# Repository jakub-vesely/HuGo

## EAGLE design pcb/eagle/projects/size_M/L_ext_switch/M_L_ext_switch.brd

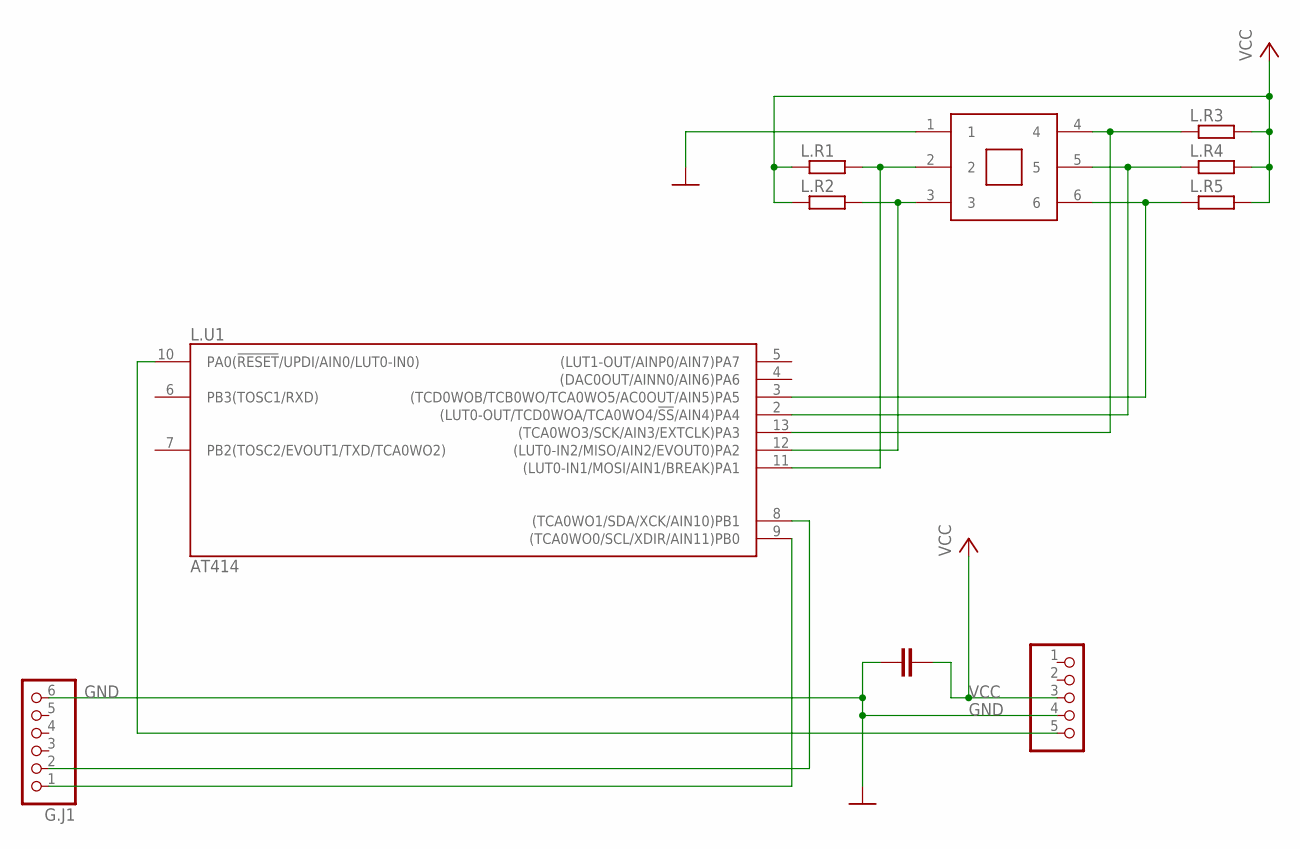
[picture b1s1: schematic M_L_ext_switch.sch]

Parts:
G.J1: PINHD-1X6; 1X06
G.J2: PINHD-1X5; 1X05
L.C1: 100n; C0603
L.R1, L.R2, L.R3, L.R4, L.R5: R-EU_R0603; R0603
L.SW1: 5_WAY_SWITCH
L.U1: AT414; SO14

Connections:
GND: G.J1.6, G.J2.4, L.C1.1, L.SW1.1, L.U1.14 (GND)
unnamed: G.J1.1, L.U1.9 ((TCA0WO0/SCL/XDIR/AIN11)PB0)
unnamed: G.J1.2, L.U1.8 ((TCA0WO1/SDA/XCK/AIN10)PB1)
unnamed: G.J2.5, L.U1.10 (PA0(!RESET!/UPDI/AIN0/LUT0-IN0))
unnamed: L.R5.1, L.SW1.6, L.U1.3 ((TCD0WOB/TCB0WO/TCA0WO5/AC0OUT/AIN5)PA5)
unnamed: L.R4.1, L.SW1.5, L.U1.2 ((LUT0-OUT/TCD0WOA/TCA0WO4/!SS!/AIN4)PA4)
unnamed: L.R3.1, L.SW1.4, L.U1.13 ((TCA0WO3/SCK/AIN3/EXTCLK)PA3)
unnamed: L.R2.2, L.SW1.3, L.U1.12 ((LUT0-IN2/MISO/AIN2/EVOUT0)PA2)
unnamed: L.R1.2, L.SW1.2, L.U1.11 ((LUT0-IN1/MOSI/AIN1/BREAK)PA1)
VCC: G.J2.3, L.C1.2, L.R1.1, L.R2.1, L.R3.2, L.R4.2, L.R5.2, L.U1.1 (VCC)

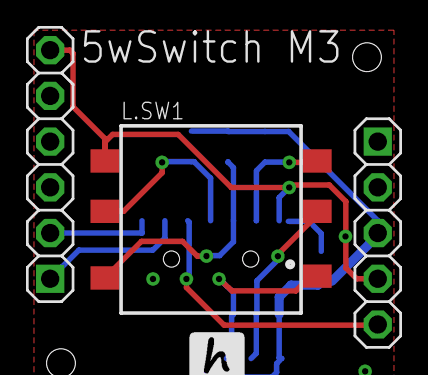
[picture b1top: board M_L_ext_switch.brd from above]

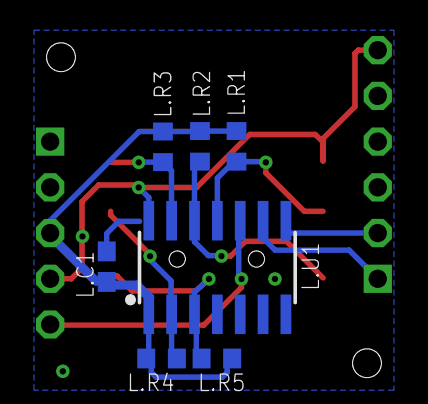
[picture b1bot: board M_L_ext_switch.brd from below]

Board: 2 copper layers, 10 parts (7 on the bottom side), 10 nets.

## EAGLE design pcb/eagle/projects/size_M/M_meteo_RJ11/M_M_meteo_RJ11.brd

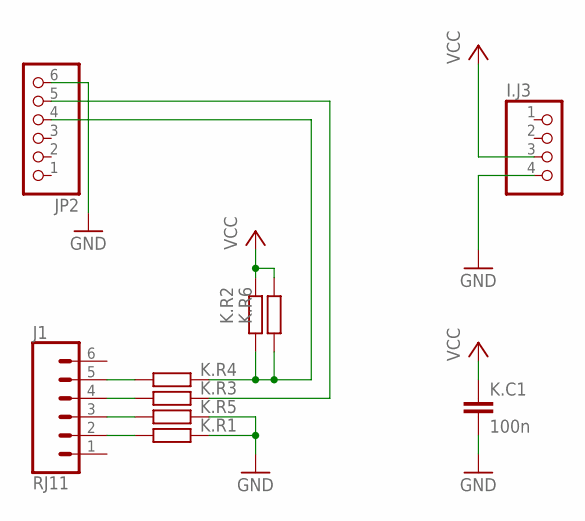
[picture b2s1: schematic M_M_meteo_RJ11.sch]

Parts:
I.J3: PINHD-1X4; 1X04
J1: RJ11; RJ11-6
JP2: PINHD-1X6; 1X06
K.C1: 100n; C0603
K.R1, K.R3, K.R4, K.R5: 1k; R0603
K.R2, K.R6: 4k7; R0603

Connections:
GND: I.J3.4, JP2.6, K.C1.2, K.R1.1, K.R5.1
unnamed: J1.5, K.R4.2
unnamed: JP2.5, K.R3.1
unnamed: JP2.4, K.R2.2, K.R4.1, K.R6.2
unnamed: J1.4, K.R3.2
unnamed: J1.3, K.R5.2
unnamed: J1.2, K.R1.2
VCC: I.J3.3, K.C1.1, K.R2.1, K.R6.1

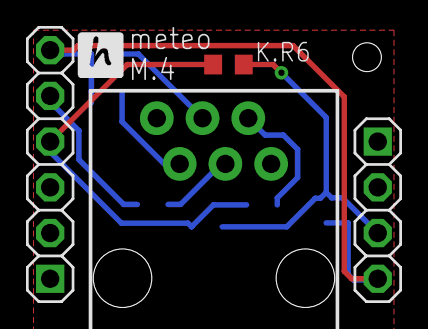
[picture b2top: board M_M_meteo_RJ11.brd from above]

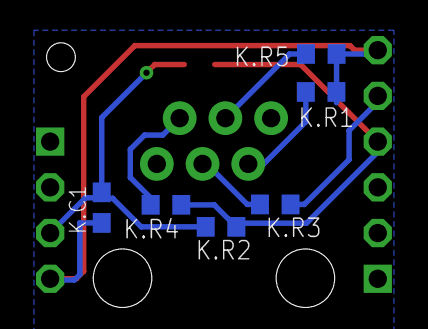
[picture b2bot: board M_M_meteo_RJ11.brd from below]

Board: 2 copper layers, 10 parts (6 on the bottom side), 8 nets.

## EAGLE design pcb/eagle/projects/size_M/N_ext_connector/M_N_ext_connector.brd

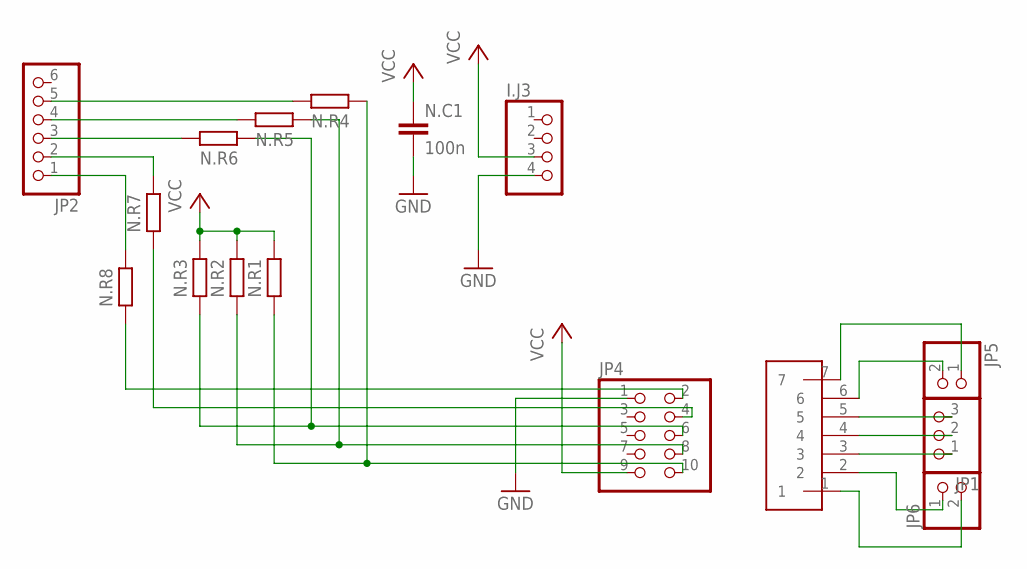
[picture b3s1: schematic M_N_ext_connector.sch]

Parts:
I.J3: PINHD-1X4; 1X04
JP1: PINHD-1X3; 1X03
JP2: PINHD-1X6; 1X06
JP4: PINHD-2X5/90; 2X05/90
JP5, JP6: PINHD-1X2; 1X02
N.C1: 100n; C0603
N.R1, N.R2, N.R3, N.R4, N.R5, N.R6, N.R7, N.R8: 4k7; R0603
U$1: 7PIN_CONNECTOR

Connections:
GND: I.J3.4, JP4.1, N.C1.2
GND1: JP5.1, U$1.7
unnamed: JP4.10, N.R1.2, N.R4.2
unnamed: JP4.8, N.R2.2, N.R5.2
unnamed: JP2.5, N.R4.1
unnamed: JP2.4, N.R5.1
unnamed: JP2.3, N.R6.1
unnamed: JP2.2, N.R7.1
unnamed: JP2.1, N.R8.1
unnamed: JP4.6, N.R3.2, N.R6.2
unnamed: JP4.4, N.R7.2
unnamed: JP4.2, N.R8.2
PA3: JP6.1, U$1.2
PA6: JP1.1, U$1.3
PA7: JP1.2, U$1.4
SCL1: JP5.2, U$1.6
SDA1: JP1.3, U$1.5
VCC: I.J3.3, JP4.9, N.C1.1, N.R1.1, N.R2.1, N.R3.1
VCC1: JP6.2, U$1.1

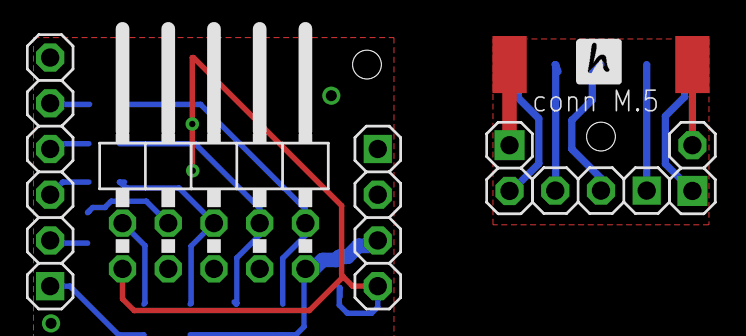
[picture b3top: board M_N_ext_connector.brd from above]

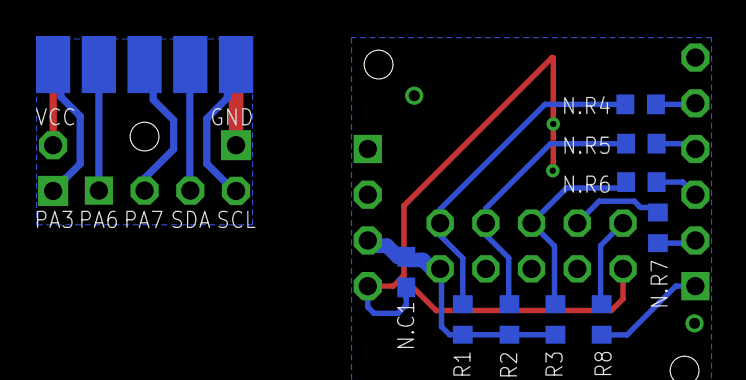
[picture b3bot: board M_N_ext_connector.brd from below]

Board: 2 copper layers, 16 parts (9 on the bottom side), 19 nets.

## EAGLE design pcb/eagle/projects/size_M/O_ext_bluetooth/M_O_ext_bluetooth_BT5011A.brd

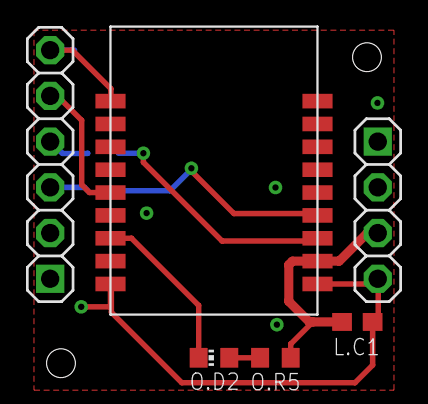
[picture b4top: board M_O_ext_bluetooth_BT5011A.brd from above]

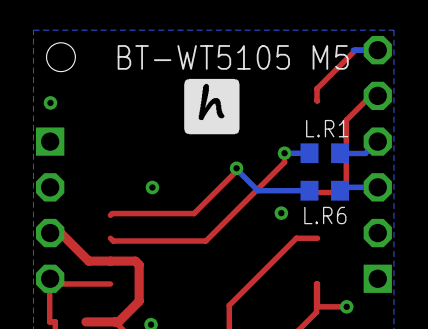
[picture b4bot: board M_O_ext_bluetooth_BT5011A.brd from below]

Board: 2 copper layers, 8 parts (2 on the bottom side), 9 nets.

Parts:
G.J1: 1X06
G.J2: 1X04
L.C1: 100n; C0603
L.R1, L.R6: 2k2; R0603
O.D2: CHIP-LED0603
O.R5: 2k2; R0603
U$1: E104-BT5011A

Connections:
GND: G.J1.6, G.J2.4, L.C1.1, U$1.GND1, U$1.GND2, U$1.GND3
unnamed: L.R6.1, U$1.TXD
unnamed: G.J1.4, L.R1.2
unnamed: L.R1.1, U$1.RXD
unnamed: G.J1.5, U$1.WKP
unnamed: O.D2.C1, U$1.LINK
unnamed: O.D2.A1, O.R5.1
VCC: G.J2.3, L.C1.2, O.R5.2, U$1.VCC
VCC1: G.J1.3, L.R6.2

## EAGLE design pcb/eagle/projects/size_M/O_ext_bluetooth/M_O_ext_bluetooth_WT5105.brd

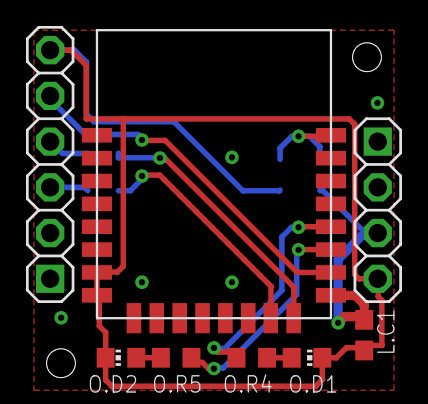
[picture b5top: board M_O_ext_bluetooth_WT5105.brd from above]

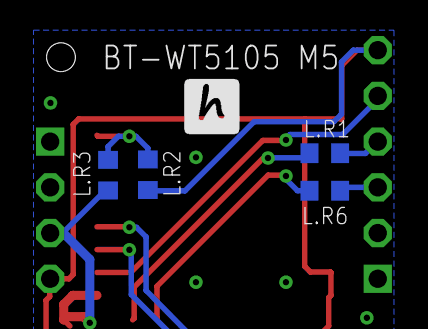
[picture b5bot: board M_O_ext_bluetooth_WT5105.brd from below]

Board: 2 copper layers, 12 parts (4 on the bottom side), 12 nets.

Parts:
G.J1: 1X06
G.J2: 1X04
L.C1: 100n; C0603
L.R1, L.R2, L.R3, L.R6: 2k2; R0603
O.D1, O.D2: CHIP-LED0603
O.R4, O.R5: 2k2; R0603
U$1: WT5105-M1

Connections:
GND: G.J1.6, G.J2.4, L.C1.1, L.R2.1, O.D1.C1, O.D2.C1, U$1.GND1, U$1.GND2
unnamed: G.J1.4, L.R1.2
unnamed: L.R1.1, U$1.P10
unnamed: G.J1.5, U$1.P14
unnamed: L.R2.2, L.R3.2, U$1.RST
unnamed: O.R4.2, U$1.P20
unnamed: L.R6.1, U$1.P09
unnamed: O.R5.2, U$1.P15
unnamed: O.D1.A1, O.R4.1
unnamed: O.D2.A1, O.R5.1
VCC: G.J2.3, L.C1.2, L.R3.1, U$1.VCC
VCC1: G.J1.3, L.R6.2

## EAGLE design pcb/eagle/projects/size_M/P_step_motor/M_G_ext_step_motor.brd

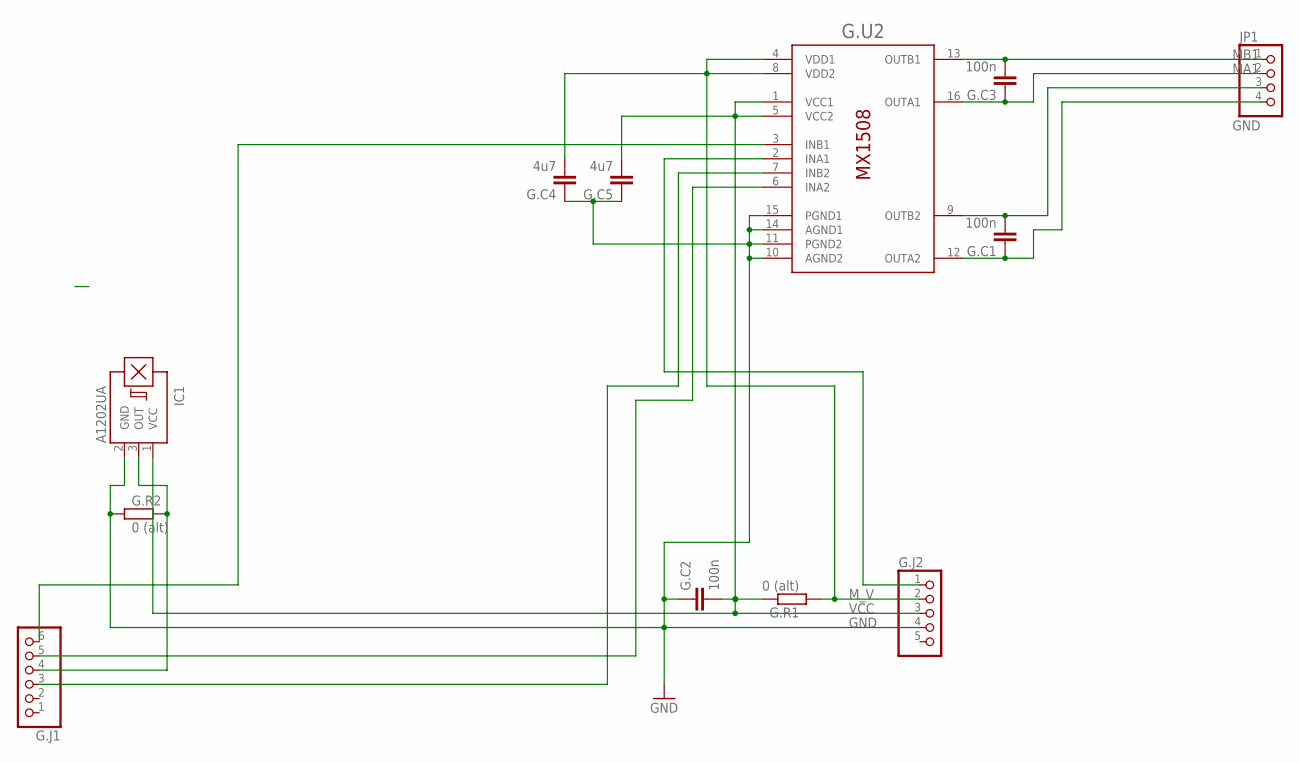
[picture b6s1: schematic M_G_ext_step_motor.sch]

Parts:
G.C1, G.C2, G.C3: 100n; C0603
G.C4, G.C5: 4u7; C0603
G.J1: PINHD-1X6; 1X06
G.J2: PINHD-1X5; 1X05
G.R1, G.R2: 0 (alt); R0603
G.U2: MX1508; SOP16
IC1: A1202UA; SIP3-UA
JP1: PINHD-1X4; 1X04

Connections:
GND: G.C2.1, G.C4.1, G.C5.1, G.J2.4, G.R2.1, G.U2.10 (AGND2), G.U2.11 (PGND2), G.U2.14 (AGND1), G.U2.15 (PGND1), IC1.2 (GND)
INA1: G.J2.1, G.U2.2 (INA1)
INA2: G.J1.5, G.U2.6 (INA2)
INB1: G.J1.6, G.U2.3 (INB1)
INB2: G.J1.3, G.U2.7 (INB2)
MA1: G.C3.1, G.U2.16 (OUTA1), JP1.2
MA2: G.C1.1, G.U2.12 (OUTA2), JP1.4
MB1: G.C3.2, G.U2.13 (OUTB1), JP1.1
MB2: G.C1.2, G.U2.9 (OUTB2), JP1.3
M_V: G.C4.2, G.J2.2, G.R1.1, G.U2.4 (VDD1), G.U2.8 (VDD2)
unnamed: G.J1.4, G.R2.2, IC1.3 (OUT)
VCC: G.C2.2, G.C5.2, G.J2.3, G.R1.2, G.U2.1 (VCC1), G.U2.5 (VCC2), IC1.1 (VCC)

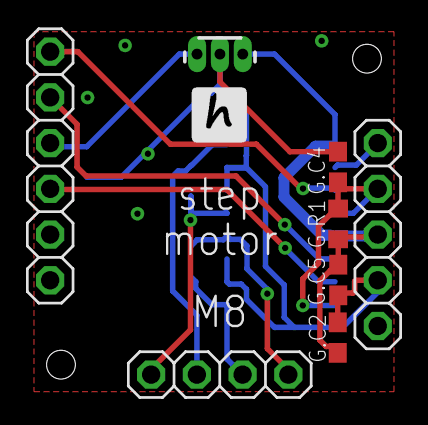
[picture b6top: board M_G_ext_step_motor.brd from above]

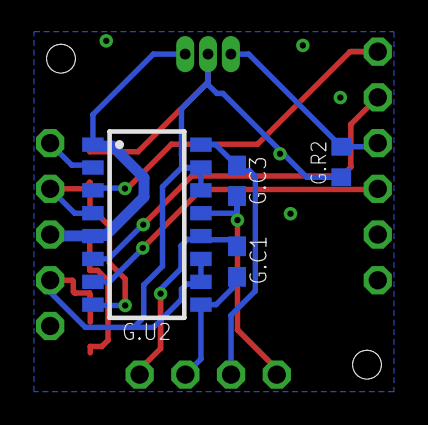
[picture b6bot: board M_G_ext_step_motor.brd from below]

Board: 2 copper layers, 12 parts (4 on the bottom side), 12 nets.

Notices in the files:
parts and their libraries:
SparkFun-Connectors: Licensing: Creative Commons ShareAlike 4.0 International - https://creativecommons.org/licenses/by-sa/4.0
